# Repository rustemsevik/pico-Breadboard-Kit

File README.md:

# Pico Breadboard Kit

This is a Raspberry Pi Pico breadboard kit designed for students to learn and experiment with basic electronics and microcontroller programming.

## Features

- **Raspberry Pi Pico** with full GPIO breakout  
- **Four tactile buttons** connected to GPIOs  
- **Four LEDs** with current-limiting resistors  
- **Buzzer** controlled via transistor switch  
- **Rotary encoder with push switch** for interactive input  
- **Potentiometer** connected to ADC input  
- **Headers for external 3.3V and 5V power**  
- **Dedicated I2C connector for screen (SCL/SDA)**  
- **Connector for MPU6050 (I2C accelerometer/gyroscope)**  
- **Servo motor headers (2x) with GPIO control**  
- **Neopixel header** for addressable LED strips  
- Mounting holes for mechanical stability  
- All components are laid out to be easily accessible on a standard breadboard.

## Getting Started

1. Insert the Raspberry Pi Pico into the breadboard.  
2. Connect power via USB.  
3. Upload your code using Thonny or the Pico SDK.  
4. Use the built-in components (buttons, LEDs, buzzer, potentiometer, rotary encoder, servos) to test your logic.  
5. Connect external devices (screen, MPU6050, Neopixel) via the dedicated headers.  

## Schematic

See the included [`v2/pico-breadboard.pdf`](v2/pico-breadboard.pdf) for the detailed wiring.

---

This kit is ideal for beginner to intermediate-level microcontroller projects, robotics experiments, and educational settings.

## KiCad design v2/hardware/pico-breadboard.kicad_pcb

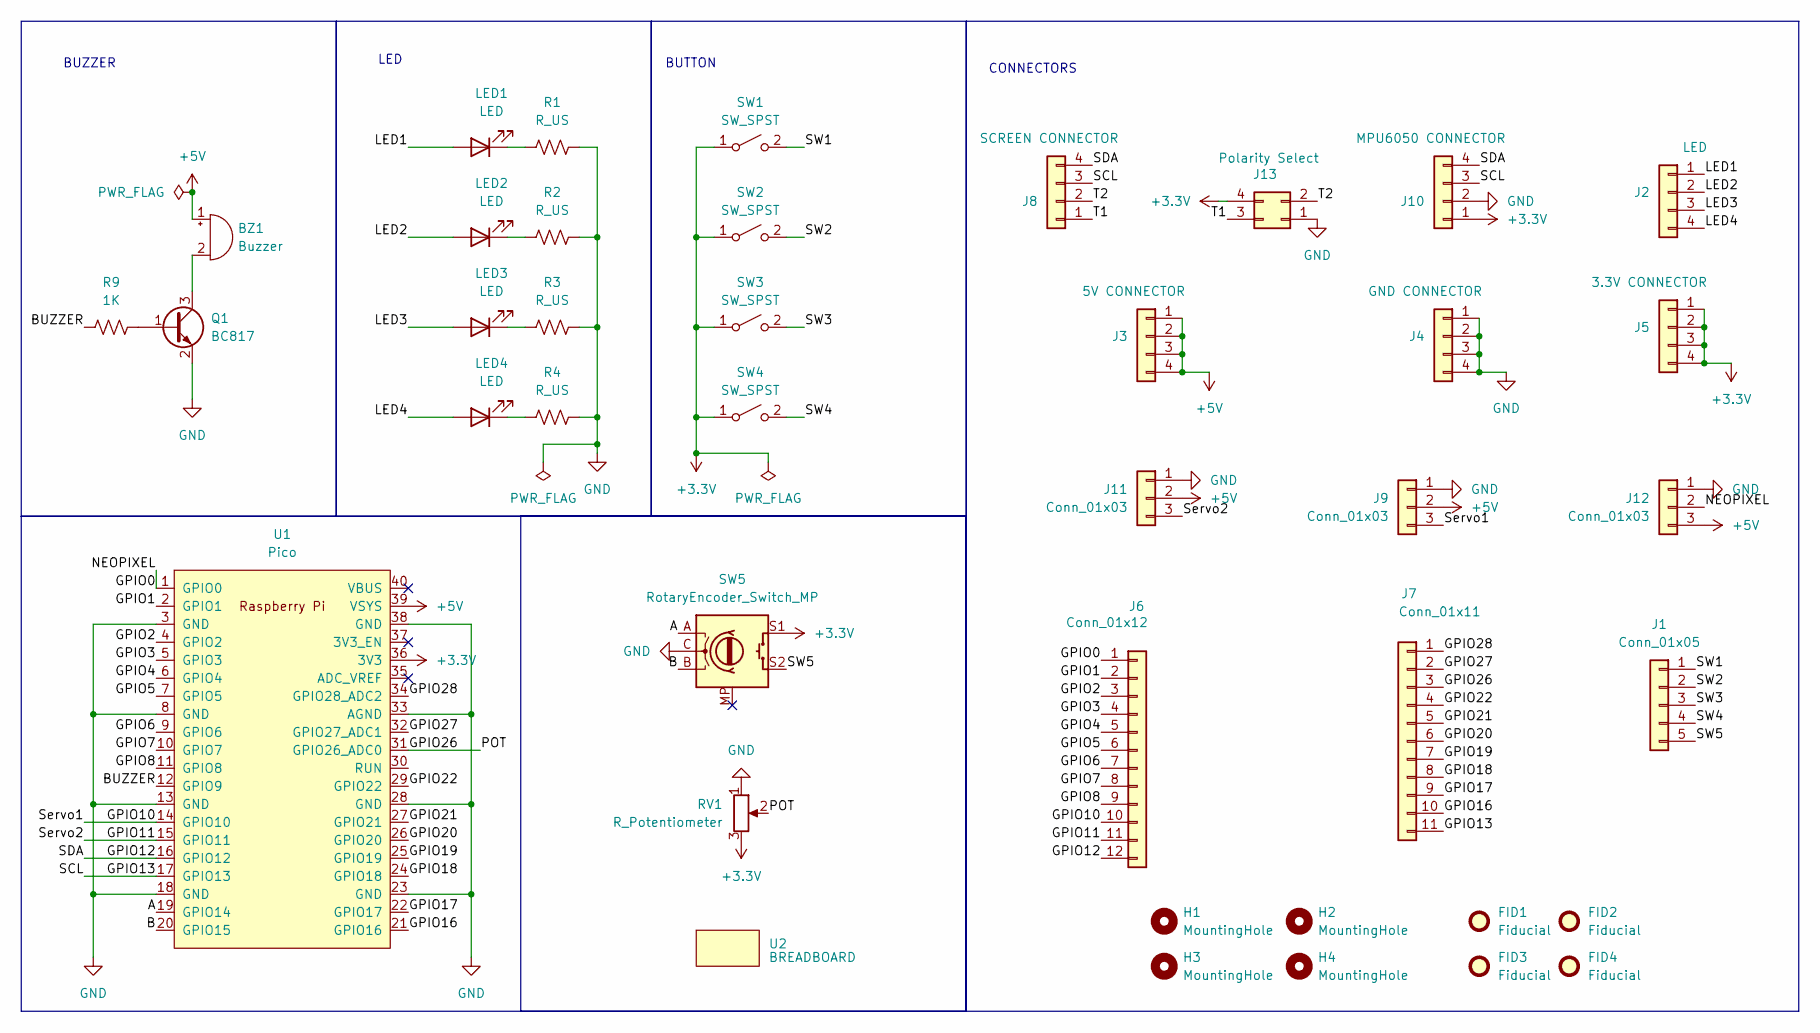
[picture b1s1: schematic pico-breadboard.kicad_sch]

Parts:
BZ1: Buzzer; Buzzer_12mm7.6
FID1, FID2, FID3, FID4: Fiducial; Fiducial_1mm_Mask2mm
H1, H2, H3, H4: MountingHole; MountingHole_3mm
J1: Conn_01x05; PinHeader_1x05_P2.54mm_Vertical
J2: LED; PinHeader_1x04_P2.54mm_Vertical
J3: 5V CONNECTOR; PinHeader_1x04_P2.54mm_Vertical
J4: GND CONNECTOR; PinHeader_1x04_P2.54mm_Vertical
J5: 3.3V CONNECTOR; PinHeader_1x04_P2.54mm_Vertical
J6: Conn_01x12; PinHeader_1x12_P2.54mm_Vertical
J7: Conn_01x11; PinHeader_1x11_P2.54mm_Vertical
J8: SCREEN CONNECTOR; PinHeader_1x04_P2.54mm_Vertical
J9, J11, J12: Conn_01x03; PinHeader_1x03_P2.54mm_Vertical
J10: MPU6050 CONNECTOR; PinHeader_1x04_P2.54mm_Vertical
J13: Polarity Select; PinHeader_2x02_P2.54mm_Vertical
LED1, LED2, LED3, LED4: LED; LED_0603_1608Metric
Q1: BC817; SOT-23
R1, R2, R3, R4: R_US; R_0402_1005Metric
R9: 1K; R_0402_1005Metric
RV1: R_Potentiometer; Potentiometer_Omeg_PC16BU_Horizontal
SW1, SW2, SW3, SW4: SW_SPST; SW_SPST_PTS810
SW5: RotaryEncoder_Switch_MP; RotaryEncoder_Alps_EC11E-Switch_Vertical_H20mm
U1: Pico; RPi_Pico_SMD_TH
U2: BREADBOARD; Breadboard

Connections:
+3.3V: J5.1, J5.2, J5.3, J5.4, J10.1, J13.4, RV1.3, SW1.1 (A), SW2.1 (A), SW3.1 (A), SW4.1 (A), SW5.S1, U1.36 (3V3)
+5V: BZ1.1 (+), J3.1, J3.2, J3.3, J3.4, J9.2, J11.2, J12.3, U1.39 (VSYS)
/A: SW5.A, U1.19 (GPIO14)
/B: SW5.B, U1.20 (GPIO15)
/BUZZER: R9.1, U1.12 (GPIO9)
/GPIO0: J6.1, J12.2, U1.1 (GPIO0)
/GPIO1: J6.2, U1.2 (GPIO1)
/GPIO2: J6.3, U1.4 (GPIO2)
/GPIO3: J6.4, U1.5 (GPIO3)
/GPIO4: J6.5, U1.6 (GPIO4)
/GPIO5: J6.6, U1.7 (GPIO5)
/GPIO6: J6.7, U1.9 (GPIO6)
/GPIO7: J6.8, U1.10 (GPIO7)
/GPIO8: J6.9, U1.11 (GPIO8)
/GPIO10: J6.10, J9.3, U1.14 (GPIO10)
/GPIO11: J6.11, J11.3, U1.15 (GPIO11)
/GPIO12: J6.12, J8.4, J10.4, U1.16 (GPIO12)
/GPIO13: J7.11, J8.3, J10.3, U1.17 (GPIO13)
/GPIO16: J7.10, U1.21 (GPIO16)
/GPIO17: J7.9, U1.22 (GPIO17)
/GPIO18: J7.8, U1.24 (GPIO18)
/GPIO19: J7.7, U1.25 (GPIO19)
/GPIO20: J7.6, U1.26 (GPIO20)
/GPIO21: J7.5, U1.27 (GPIO21)
/GPIO22: J7.4, U1.29 (GPIO22)
/GPIO26: J7.3, RV1.2, U1.31 (GPIO26_ADC0)
/GPIO27: J7.2, U1.32 (GPIO27_ADC1)
/GPIO28: J7.1, U1.34 (GPIO28_ADC2)
/LED1: J2.1, LED1.2 (A)
/LED2: J2.2, LED2.2 (A)
/LED3: J2.3, LED3.2 (A)
/LED4: J2.4, LED4.2 (A)
/SW1: J1.1, SW1.2 (B)
/SW2: J1.2, SW2.2 (B)
/SW3: J1.3, SW3.2 (B)
/SW4: J1.4, SW4.2 (B)
/SW5: J1.5, SW5.S2
/T1: J8.1, J13.3
/T2: J8.2, J13.2
GND: J4.1, J4.2, J4.3, J4.4, J9.1, J10.2, J11.1, J12.1, J13.1, Q1.2 (E), R1.2, R2.2, R3.2, R4.2, RV1.1, SW5.C, U1.3 (GND), U1.8 (GND), U1.13 (GND), U1.18 (GND), U1.23 (GND), U1.28 (GND), U1.33 (AGND), U1.38 (GND)
unnamed: BZ1.2 (-), Q1.3 (C)
unnamed: LED1.1 (K), R1.1
unnamed: LED2.1 (K), R2.1
unnamed: LED3.1 (K), R3.1
unnamed: LED4.1 (K), R4.1
unnamed: Q1.1 (B), R9.2

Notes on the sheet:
BUTTON
CONNECTORS
LED
BUZZER

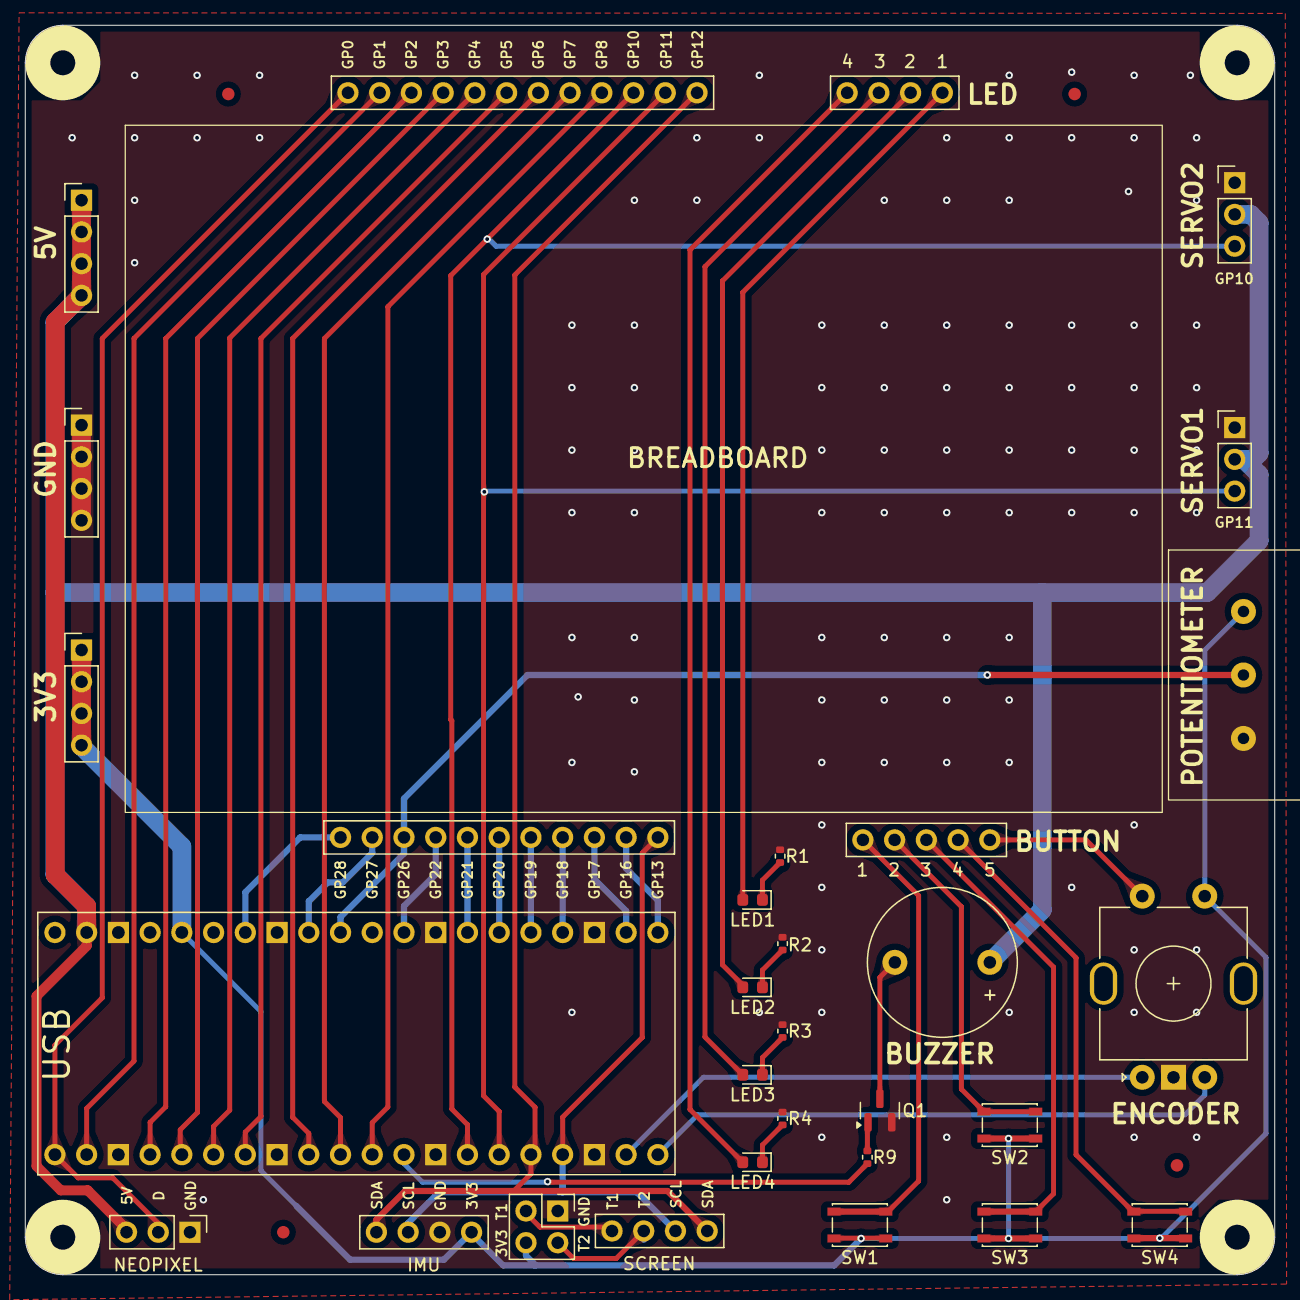
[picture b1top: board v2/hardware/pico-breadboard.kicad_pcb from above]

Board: 2 copper layers, 100.0 x 100.0 mm, 40 parts (1 on the bottom side), 46 nets.

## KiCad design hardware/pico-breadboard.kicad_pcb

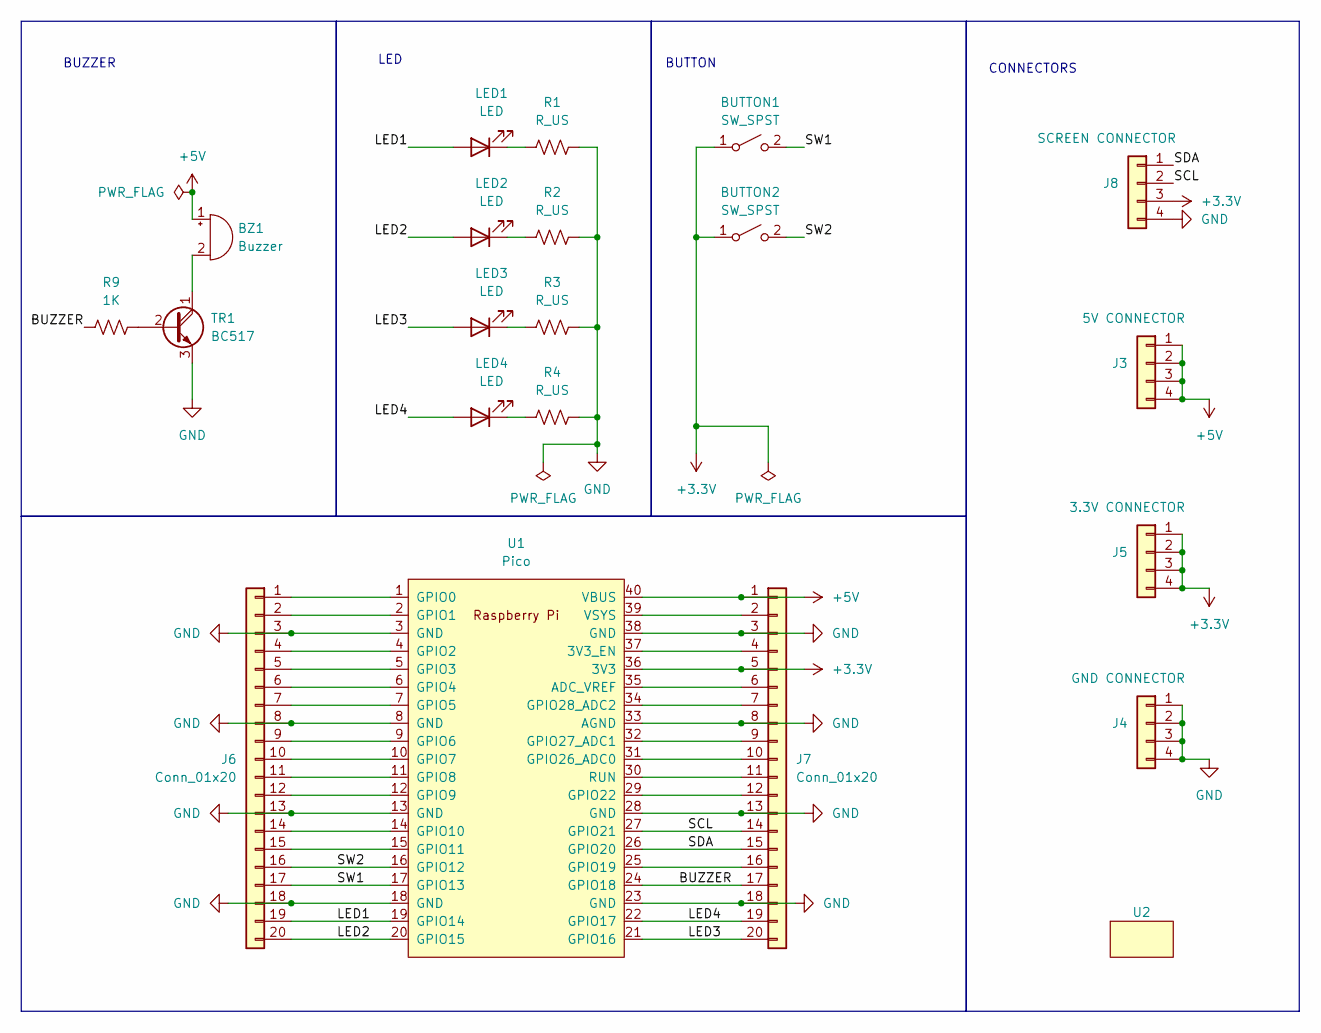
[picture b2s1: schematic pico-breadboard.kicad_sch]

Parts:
BUTTON1, BUTTON2: SW_SPST; SW_PUSH_6mm
BZ1: Buzzer; Buzzer_15x7.5RM7.6
J3: 5V CONNECTOR; PinHeader_1x04_P2.54mm_Vertical
J4: GND CONNECTOR; PinHeader_1x04_P2.54mm_Vertical
J5: 3.3V CONNECTOR; PinHeader_1x04_P2.54mm_Vertical
J6, J7: Conn_01x20; PinHeader_1x20_P2.54mm_Vertical
J8: SCREEN CONNECTOR; PinHeader_1x04_P2.54mm_Vertical
LED1, LED2, LED3, LED4: LED; LED_D5.0mm
R1, R2, R3, R4: R_US; R_Axial_DIN0204_L3.6mm_D1.6mm_P7.62mm_Horizontal
R9: 1K; R_Axial_DIN0204_L3.6mm_D1.6mm_P7.62mm_Horizontal
TR1: BC517; TO-92_Inline
U1: Pico; RPi_Pico_SMD_TH
U2: Breadboard

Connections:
+3.3V: BUTTON1.1 (A), BUTTON2.1 (A), J5.1, J5.2, J5.3, J5.4, J7.5, J8.3, U1.36 (3V3)
+5V: BZ1.1 (+), J3.1, J3.2, J3.3, J3.4, J7.1, U1.40 (VBUS)
/BUZZER: J7.17, R9.1, U1.24 (GPIO18)
/LED1: J6.19, LED1.2 (A), U1.19 (GPIO14)
/LED2: J6.20, LED2.2 (A), U1.20 (GPIO15)
/LED3: J7.20, LED3.2 (A), U1.21 (GPIO16)
/LED4: J7.19, LED4.2 (A), U1.22 (GPIO17)
/SCL: J7.14, J8.2, U1.27 (GPIO21)
/SDA: J7.15, J8.1, U1.26 (GPIO20)
/SW1: BUTTON1.2 (B), J6.17, U1.17 (GPIO13)
/SW2: BUTTON2.2 (B), J6.16, U1.16 (GPIO12)
GND: J4.1, J4.2, J4.3, J4.4, J6.3, J6.8, J6.13, J6.18, J7.3, J7.8, J7.13, J7.18, J8.4, R1.2, R2.2, R3.2, R4.2, TR1.3 (E), U1.3 (GND), U1.8 (GND), U1.13 (GND), U1.18 (GND), U1.23 (GND), U1.28 (GND), U1.33 (AGND), U1.38 (GND)
unnamed: BZ1.2 (-), TR1.1 (C)
unnamed: J6.1, U1.1 (GPIO0)
unnamed: J6.2, U1.2 (GPIO1)
unnamed: J6.4, U1.4 (GPIO2)
unnamed: J6.5, U1.5 (GPIO3)
unnamed: J6.6, U1.6 (GPIO4)
unnamed: J6.7, U1.7 (GPIO5)
unnamed: J6.9, U1.9 (GPIO6)
unnamed: J6.10, U1.10 (GPIO7)
unnamed: J6.11, U1.11 (GPIO8)
unnamed: J6.12, U1.12 (GPIO9)
unnamed: J6.14, U1.14 (GPIO10)
unnamed: J6.15, U1.15 (GPIO11)
unnamed: J7.2, U1.39 (VSYS)
unnamed: J7.4, U1.37 (3V3_EN)
unnamed: J7.6, U1.35 (ADC_VREF)
unnamed: J7.7, U1.34 (GPIO28_ADC2)
unnamed: J7.9, U1.32 (GPIO27_ADC1)
unnamed: J7.10, U1.31 (GPIO26_ADC0)
unnamed: J7.11, U1.30 (RUN)
unnamed: J7.12, U1.29 (GPIO22)
unnamed: J7.16, U1.25 (GPIO19)
unnamed: LED1.1 (K), R1.1
unnamed: LED2.1 (K), R2.1
unnamed: LED3.1 (K), R3.1
unnamed: LED4.1 (K), R4.1
unnamed: R9.2, TR1.2 (B)

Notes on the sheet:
BUTTON
CONNECTORS
LED
BUZZER

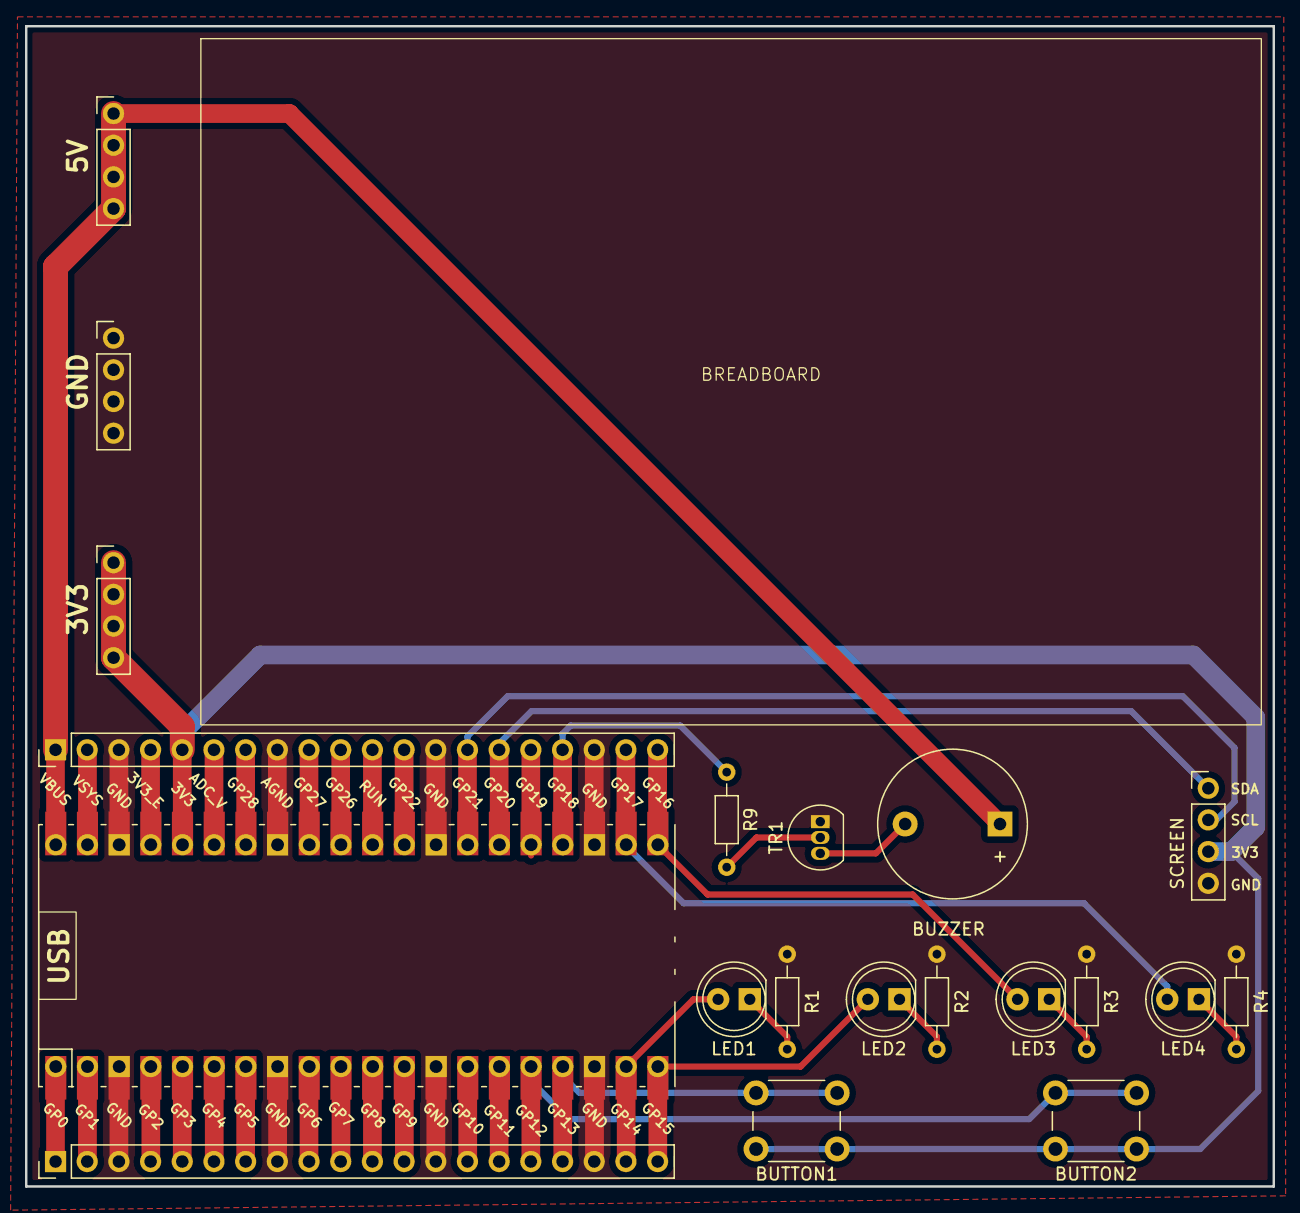
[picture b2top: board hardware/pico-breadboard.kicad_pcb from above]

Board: 2 copper layers, 100.0 x 93.0 mm, 21 parts (0 on the bottom side), 39 nets.

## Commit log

2025-08-09 Rename pico-breadboard.png to render.png
2025-08-09 Add KiCad .gitignore
2025-08-09 schematic updated
2025-08-09 minor changes
2025-08-11 v2 created
2025-09-08 v2 updated
2025-09-08 Rename README-V1.md to README.md
2025-10-19 silkscreen fixel board size adjusted
2025-11-21 polarity selector added
